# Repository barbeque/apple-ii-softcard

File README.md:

## Current Status
First version in development. Please check back later.

## Special Thanks
[plpg](https://polprog.net) created the original board edge and connector, which got the project off to a great start. Thank you!

Patrick Schäfer [created a cleaned-up version](https://archive.org/details/apple_schematics_Softcard) of the official Microsoft schematics (`docs/apple_schematics_softcard.pdf` in this repo.)

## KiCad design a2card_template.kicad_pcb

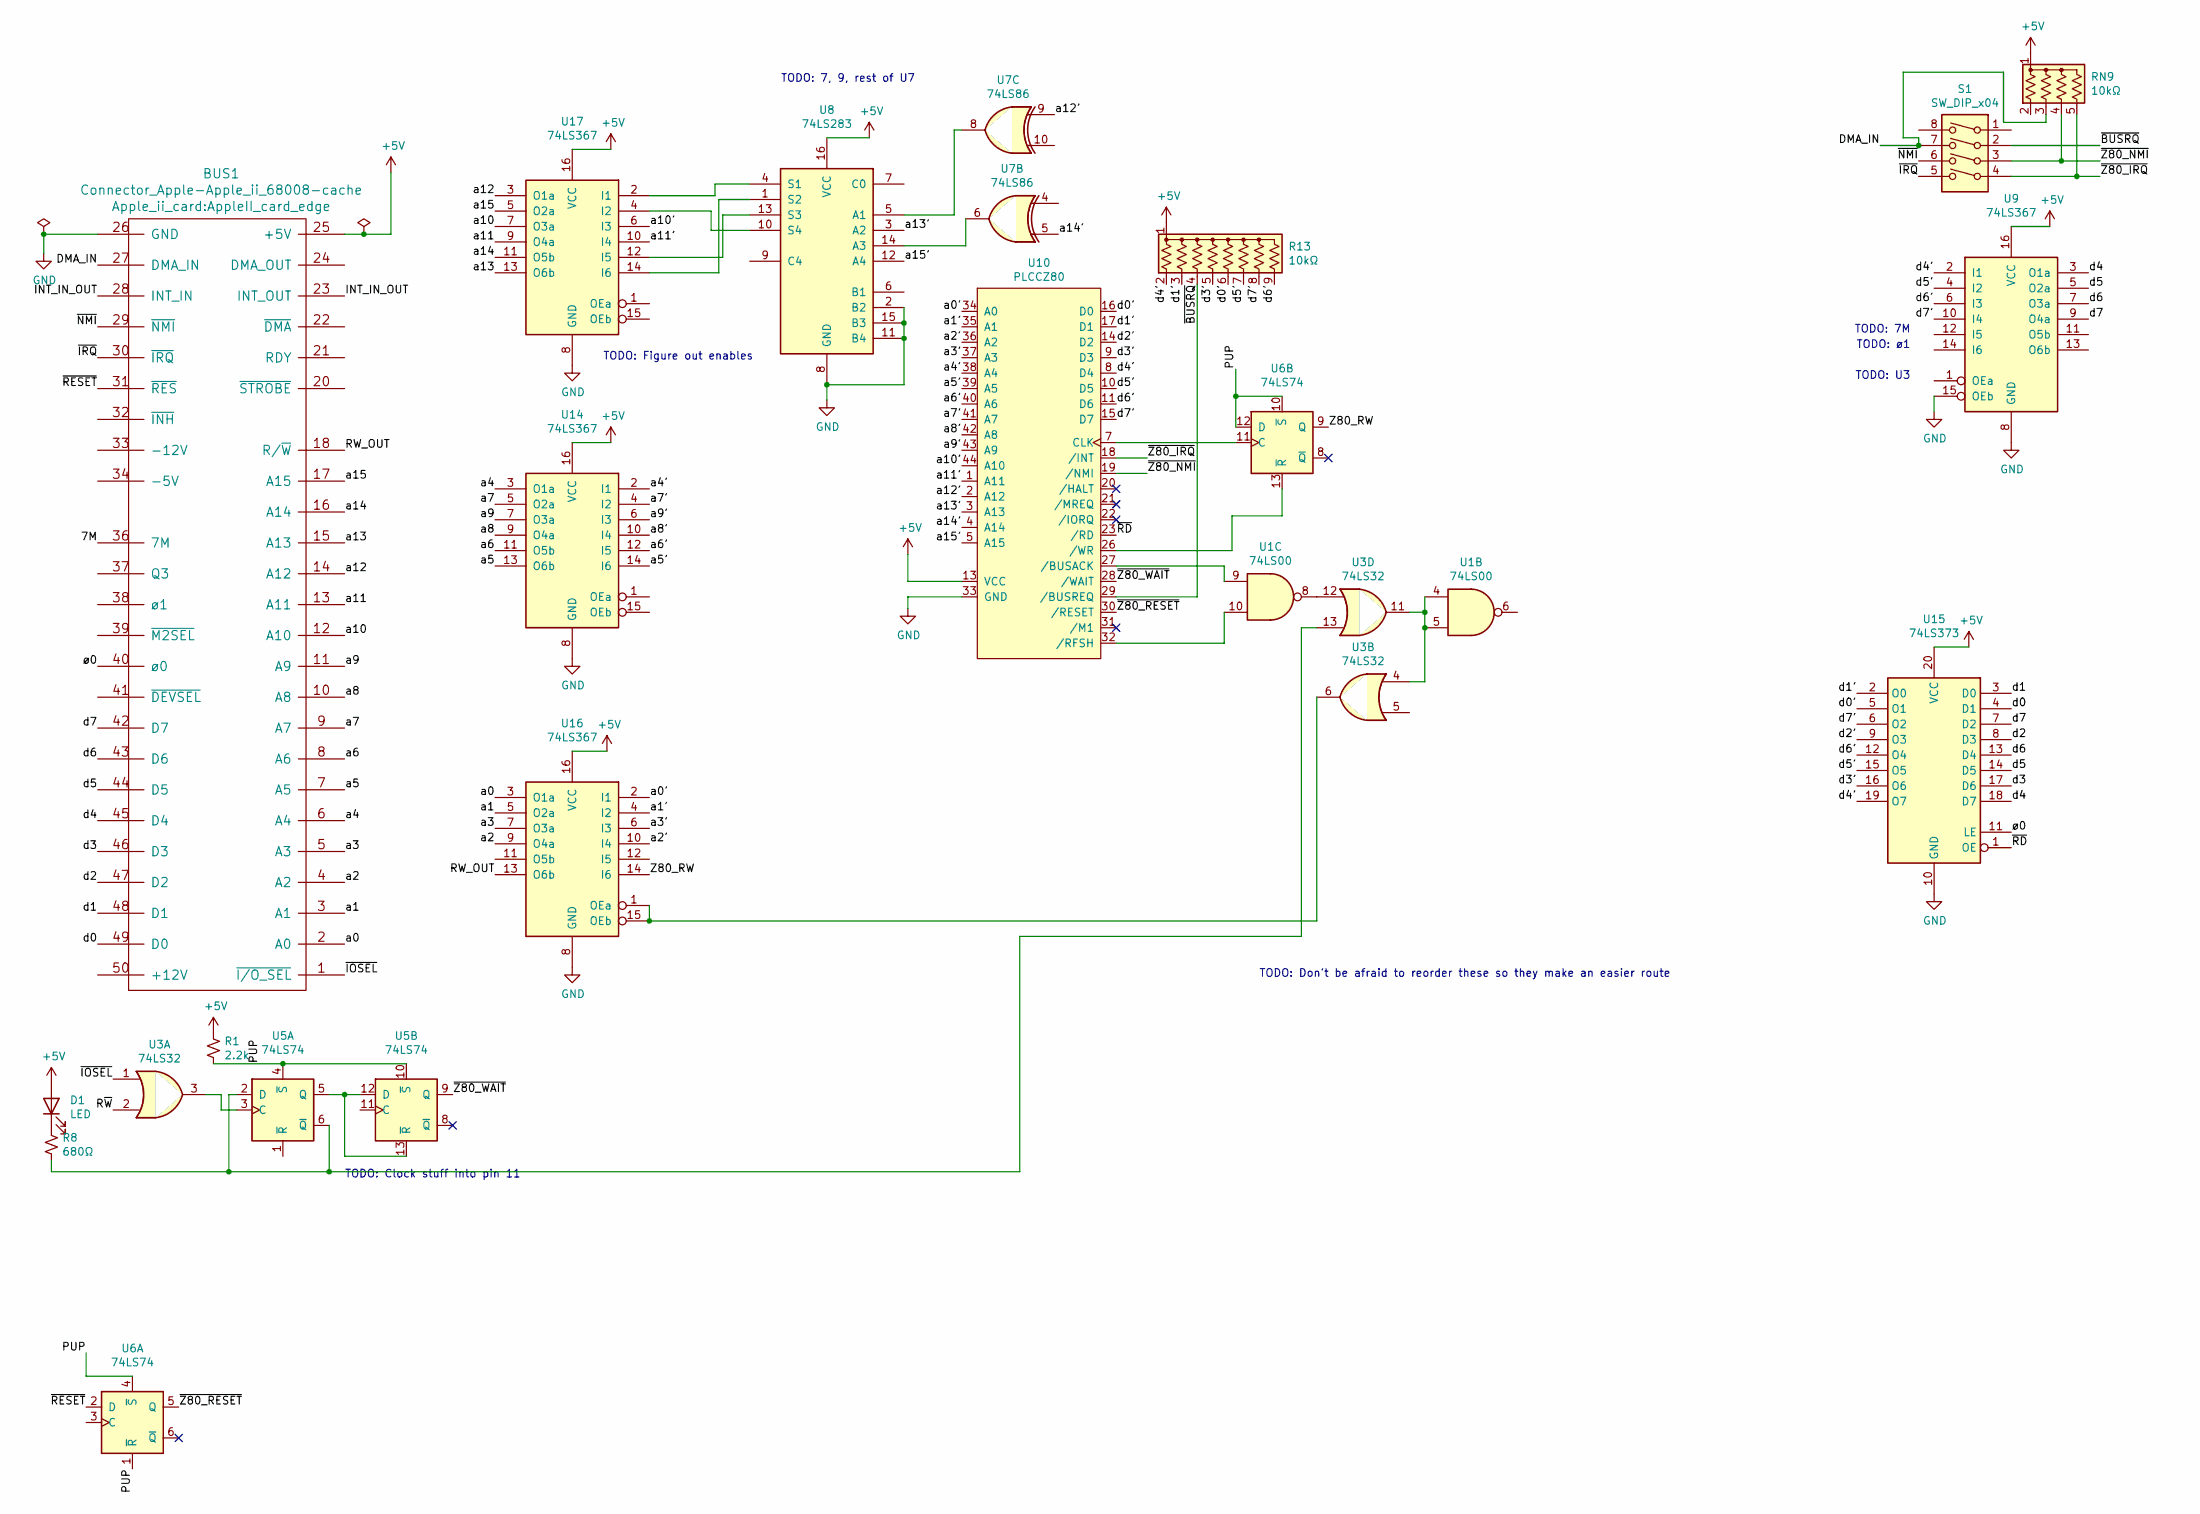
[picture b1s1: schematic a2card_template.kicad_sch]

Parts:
BUS1: Connector_Apple-Apple_ii_68008-cache; AppleII_card_edge
D1: LED; LED_D5.0mm
R1: 2.2k; R_Axial_DIN0207_L6.3mm_D2.5mm_P7.62mm_Horizontal
R8: 680Ω; R_Axial_DIN0207_L6.3mm_D2.5mm_P7.62mm_Horizontal
R13: 10kΩ; R_Array_SIP9
RN9: 10kΩ; R_Array_SIP5
S1: SW_DIP_x04; SW_DIP_SPSTx04_Slide_9.78x12.34mm_W7.62mm_P2.54mm
U1: 74LS00; DIP-14_W7.62mm
U3: 74LS32; DIP-14_W7.62mm
U5, U6: 74LS74; DIP-14_W7.62mm
U7: 74LS86; DIP-14_W7.62mm
U8: 74LS283; DIP-16_W7.62mm
U9, U14, U16, U17: 74LS367; DIP-16_W7.62mm; DigiKey 296-3701-5-ND‎
U10: PLCCZ80; PLCC-44_THT-Socket
U15: 74LS373; DIP-20_W7.62mm; DigiKey 296-1660-5-ND‎

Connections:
+5V: BUS1.25 (+5V), D1.2 (A), R1.1, R13.1 (common), RN9.1 (common), U8.16 (VCC), U9.16 (VCC), U10.13 (VCC), U14.16 (VCC), U15.20 (VCC), U16.16 (VCC), U17.16 (VCC)
/7M: BUS1.36 (7M)
/DMA_IN: BUS1.27 (DMA_IN), RN9.3 (R2), S1.7
/INT_IN_OUT: BUS1.23 (INT_OUT), BUS1.28 (INT_IN)
/PUP: R1.2, U5.4 (~S), U5.10 (~S), U6.1 (~R), U6.4 (~S), U6.10 (~S), U6.12 (D)
/RW_OUT: BUS1.18 (R/~W), U16.13 (O6b)
/R~W: U3.2
/Z80_RW: U6.9 (Q), U16.14 (I6)
/a0: BUS1.2 (A0), U16.3 (O1a)
/a0': U10.34 (A0), U16.2 (I1)
/a1: BUS1.3 (A1), U16.5 (O2a)
/a1': U10.35 (A1), U16.4 (I2)
/a2: BUS1.4 (A2), U16.9 (O4a)
/a2': U10.36 (A2), U16.10 (I4)
/a3: BUS1.5 (A3), U16.7 (O3a)
/a3': U10.37 (A3), U16.6 (I3)
/a4: BUS1.6 (A4), U14.3 (O1a)
/a4': U10.38 (A4), U14.2 (I1)
/a5: BUS1.7 (A5), U14.13 (O6b)
/a5': U10.39 (A5), U14.14 (I6)
/a6: BUS1.8 (A6), U14.11 (O5b)
/a6': U10.40 (A6), U14.12 (I5)
/a7: BUS1.9 (A7), U14.5 (O2a)
/a7': U10.41 (A7), U14.4 (I2)
/a8: BUS1.10 (A8), U14.9 (O4a)
/a8': U10.42 (A8), U14.10 (I4)
/a9: BUS1.11 (A9), U14.7 (O3a)
/a9': U10.43 (A9), U14.6 (I3)
/a10: BUS1.12 (A10), U17.7 (O3a)
/a10': U10.44 (A10), U17.6 (I3)
/a11: BUS1.13 (A11), U17.9 (O4a)
/a11': U10.1 (A11), U17.10 (I4)
/a12: BUS1.14 (A12), U17.3 (O1a)
/a12': U7.9, U10.2 (A12)
/a13: BUS1.15 (A13), U17.13 (O6b)
/a13': U8.3 (A2), U10.3 (A13)
/a14: BUS1.16 (A14), U17.11 (O5b)
/a14': U7.5, U10.4 (A14)
/a15: BUS1.17 (A15), U17.5 (O2a)
/a15': U8.12 (A4), U10.5 (A15)
/d0: BUS1.49 (D0), U15.4 (D1)
/d0': R13.6 (R5), U10.16 (D0), U15.5 (O1)
/d1: BUS1.48 (D1), U15.3 (D0)
/d1': R13.3 (R2), U10.17 (D1), U15.2 (O0)
/d2: BUS1.47 (D2), U15.8 (D3)
/d2': U10.14 (D2), U15.9 (O3)
/d3: BUS1.46 (D3), U15.17 (D6)
/d3': R13.5 (R4), U10.9 (D3), U15.16 (O6)
/d4: BUS1.45 (D4), U9.3 (O1a), U15.18 (D7)
/d4': R13.2 (R1), U9.2 (I1), U10.8 (D4), U15.19 (O7)
/d5: BUS1.44 (D5), U9.5 (O2a), U15.14 (D5)
/d5': R13.7 (R6), U9.4 (I2), U10.10 (D5), U15.15 (O5)
/d6: BUS1.43 (D6), U9.7 (O3a), U15.13 (D4)
/d6': R13.9 (R8), U9.6 (I3), U10.11 (D6), U15.12 (O4)
/d7: BUS1.42 (D7), U9.9 (O4a), U15.7 (D2)
/d7': R13.8 (R7), U9.10 (I4), U10.15 (D7), U15.6 (O2)
/~BUSRQ: R13.4 (R3), S1.2, U10.29 (/BUSREQ)
/~IOSEL: BUS1.1 (~I/O_SEL), U3.1
/~IRQ: BUS1.30 (~IRQ), S1.5
/~NMI: BUS1.29 (~NMI), S1.6
/~RD: U10.23 (/RD), U15.1 (OE)
/~RESET: BUS1.31 (~RES), U6.2 (D)
/~Z80_IRQ: RN9.5 (R4), S1.4, U10.18 (/INT)
/~Z80_NMI: RN9.4 (R3), S1.3, U10.19 (/NMI)
/~Z80_RESET: U6.5 (Q), U10.30 (/RESET)
/~Z80_WAIT: U5.9 (Q), U10.28 (/WAIT)
/ø0: BUS1.40 (ø0), U15.11 (LE)
unnamed: D1.1 (K), R8.1
unnamed: R8.2, U3.13, U5.2 (D), U5.6 (~Q)
unnamed: U1.4, U1.5, U3.4, U3.11
unnamed: U1.8, U3.12
unnamed: U1.9, U10.27 (/BUSACK)
unnamed: U1.10, U10.32 (/RFSH)
unnamed: U3.3, U5.3 (C)
unnamed: U5.5 (Q), U5.12 (D), U5.13 (~R)
unnamed: U7.6, U8.14 (A3)
unnamed: U7.8, U8.5 (A1)
unnamed: U6.11 (C), U10.7 (CLK)
unnamed: U6.13 (~R), U10.26 (/WR)
unnamed: U3.6, U16.1 (OEa), U16.15 (OEb)
unnamed: U8.4 (S1), U17.2 (I1)
unnamed: U8.10 (S4), U17.4 (I2)
unnamed: U8.13 (S3), U17.12 (I5)
unnamed: U8.1 (S2), U17.14 (I6)

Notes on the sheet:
TODO: 7, 9, rest of U7
TODO: Don't be afraid to reorder these so they make an easier route
TODO: 7M
TODO: Clock stuff into pin 11
TODO: ø1
TODO: Figure out enables
TODO: U3

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
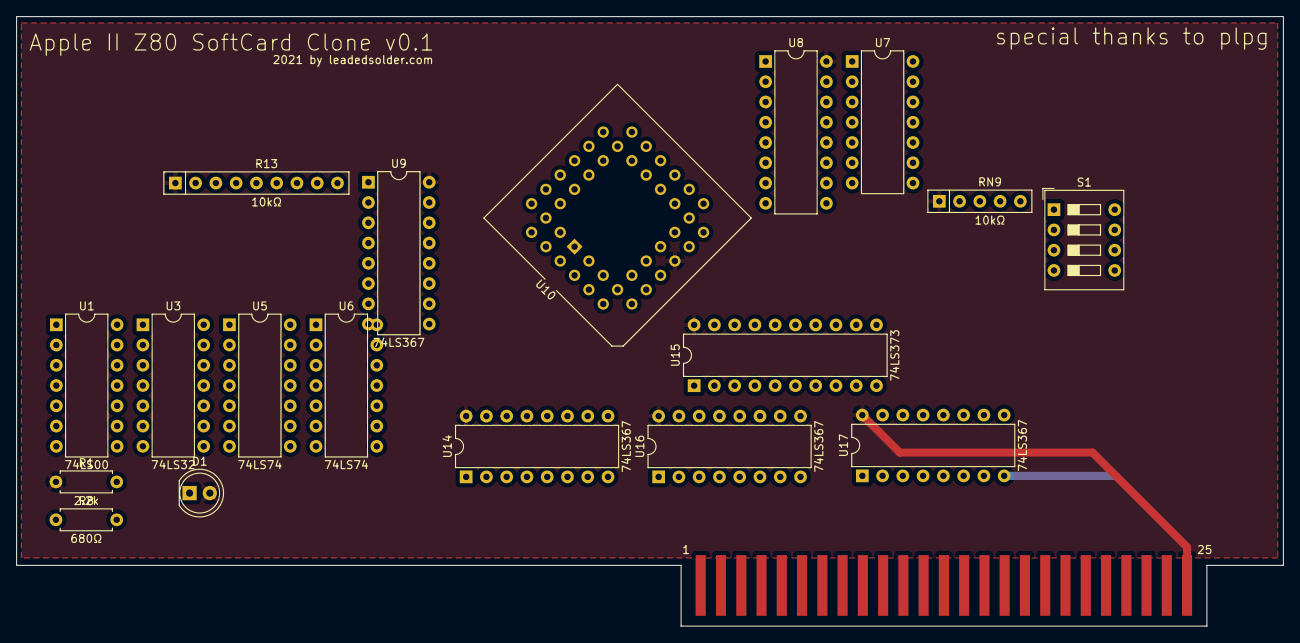
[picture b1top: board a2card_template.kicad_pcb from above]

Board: 2 copper layers, 158.8 x 76.4 mm, 19 parts (0 on the bottom side), 83 nets.

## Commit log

2021-09-30 Synchronized edge with schematic
2021-09-30 README
2021-09-30 Silk repair
2021-09-30 Landed the Leako PLCC Z80
2021-10-01 Filling in the schemaitc
2021-10-01 Add data-bus latch
2021-10-01 Fix reference for U15
2021-10-01 Configuration DIP
2021-10-01 Popping more junk
2021-10-01 Cleaning up footprints
2021-10-02 Flip the connector so 1-25 are on the front
2021-10-02 Move fingers up so it can be beveled
2021-10-02 Flip fills
2021-10-02 More fill cleanup
2021-10-02 Pin numbers
2021-10-02 a couple 7474s added
2021-10-02 More ICs placed
2021-10-03 Add u8, part of u7
2023-12-20 KiCad Upgrade
2023-12-20 Add partial 74367 symbol, populate top row of schem
2023-12-20 Clean up edge symbol
2023-12-23 In progress
